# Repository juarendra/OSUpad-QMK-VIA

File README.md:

<div align="center">

# OSUpad Clone VIA

**Macropad 6 tombol hotswap + tactile dengan RGB — konfigurasi tombol, layer,
macro, dan efek RGB lewat VIA, tanpa driver tambahan.**

oleh [Juarendra Ramadhani](https://github.com/juarendra)

[📦 Unduh Firmware](https://github.com/juarendra/OSUpad-QMK-VIA/releases/latest) |
[📖 Panduan Pengguna](DOC/PANDUAN_OSUPAD.md) |
[💻 Buka VIA](https://usevia.app) |
[🛠️ Hardware](HARDWARE)

</div>

---

Firmware alternatif berbasis Arduino (VIA-Arduino) untuk *clone* Macropad OSUpad 2x3. Ditujukan untuk *board clone* STM32F103 (dengan flash 32KB/64KB/256KB) yang jalur USB-nya tidak stabil ketika menggunakan firmware QMK/ChibiOS bawaan.

- **Protokol Stabil:** Menggunakan *USB stack* `STM32duino/libmaple` yang teruji stabil untuk clone STM32.
- **Auto-Detect VIA:** Menggunakan USB VID `0x7877` dan PID `0x1000` (sama dengan QMK). Memungkinkan *auto-detect* di aplikasi VIA jika *cache* definisi sudah ada di browser Anda.
- **Lighting Responsif:** Dukungan penuh tab Lighting di VIA V3 dengan efek `qmk_rgblight` dan optimasi *timing* bit-bang khusus untuk LED WS2812 di clock 72MHz.
- **Penyimpanan Aman:** Dual-page Flash Storage melindungi konfigurasi Anda dari kerusakan data jika USB tiba-tiba dicabut.

## Panduan Cepat

1. Unduh rilis `.bin` terbaru dan ikuti panduan **[Flash ST-Link](FIRMWARE/OSUpadCloneVIA/FLASH_STLINK.md)**.
2. Cabut ST-Link, colok kabel USB, lalu buka [usevia.app](https://usevia.app).
3. Jika *auto-detect* gagal, buka tab **Settings**, aktifkan **Show Design Tab**, lalu *load* `via-definition.json` yang ada di rilis. Pastikan opsi *Use V2 definitions* dinonaktifkan.
4. Jangan lupa baca **[Buku Panduan OSUpad](DOC/PANDUAN_OSUPAD.md)** untuk referensi layer dan kustomisasi.

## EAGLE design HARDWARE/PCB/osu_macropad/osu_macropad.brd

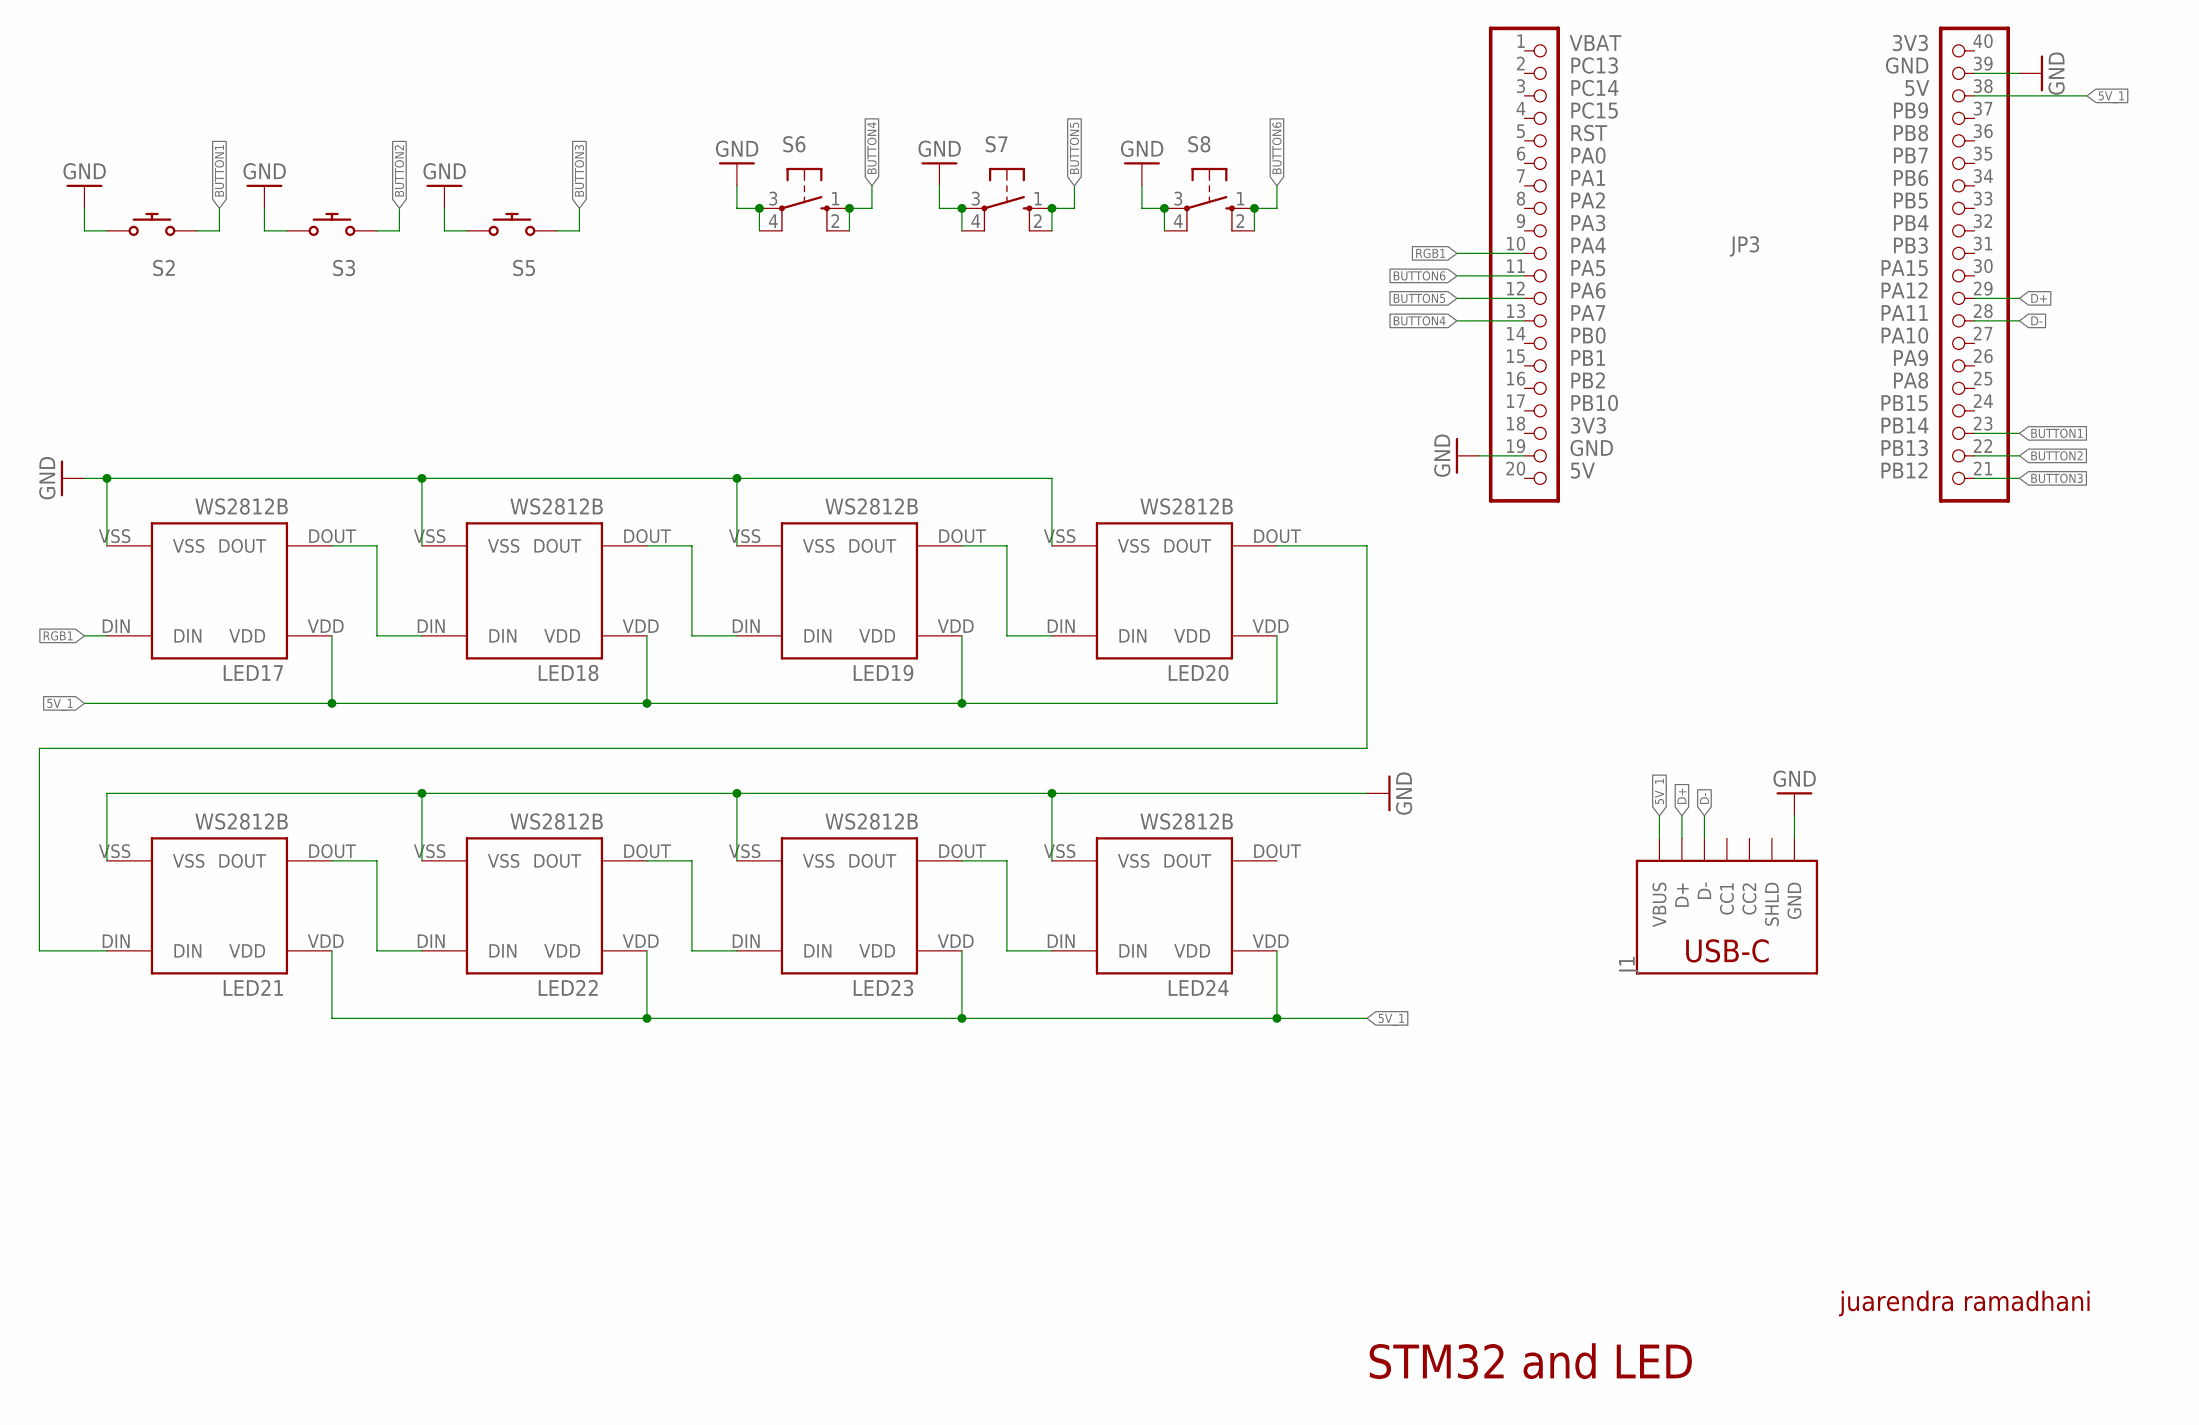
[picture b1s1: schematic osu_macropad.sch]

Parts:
J1: USB_C_2-LAYER_PADS; USB-C-16P-2LAYER-PADS
JP3: PINHD-1X20; 1X20
LED17, LED18, LED19, LED20, LED21, LED22, LED23, LED24: WS2812B
S2, S3, S5: CHERRY_MX_WITH_KEILWITH_KEIL; CHERRY_MX_WITH_KEIL
S6, S7, S8: 10-XX; B3F-10XX

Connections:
5V_1: J1.VBUS1 (VBUS), J1.VBUS2 (VBUS), JP3.38, LED17.VDD, LED18.VDD, LED19.VDD, LED20.VDD, LED21.VDD, LED22.VDD, LED23.VDD, LED24.VDD
BUTTON1: JP3.23, S2.2, S2.4 (2)
BUTTON2: JP3.22, S3.2, S3.4 (2)
BUTTON3: JP3.21, S5.2, S5.4 (2)
BUTTON4: JP3.13, S6.1 (S), S6.2 (S1)
BUTTON5: JP3.12, S7.1 (S), S7.2 (S1)
BUTTON6: JP3.11, S8.1 (S), S8.2 (S1)
D+: J1.A6 (D+), J1.B6 (D+), JP3.29
D-: J1.A7 (D-), J1.B7 (D-), JP3.28
GND: J1.GND, J1.GND2 (GND), JP3.19, JP3.39, LED17.VSS, LED18.VSS, LED19.VSS, LED20.VSS, LED21.VSS, LED22.VSS, LED23.VSS, LED24.VSS, S2.1, S2.3 (1), S3.1, S3.3 (1), S5.1, S5.3 (1), S6.3, S6.4 (P1), S7.3, S7.4 (P1), S8.3, S8.4 (P1)
unnamed: LED19.DOUT, LED20.DIN
unnamed: LED17.DOUT, LED18.DIN
unnamed: LED20.DOUT, LED21.DIN
unnamed: LED18.DOUT, LED19.DIN
unnamed: LED21.DOUT, LED22.DIN
unnamed: LED22.DOUT, LED23.DIN
unnamed: LED23.DOUT, LED24.DIN
RGB1: JP3.10, LED17.DIN

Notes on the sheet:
STM32 and LED
juarendra ramadhani

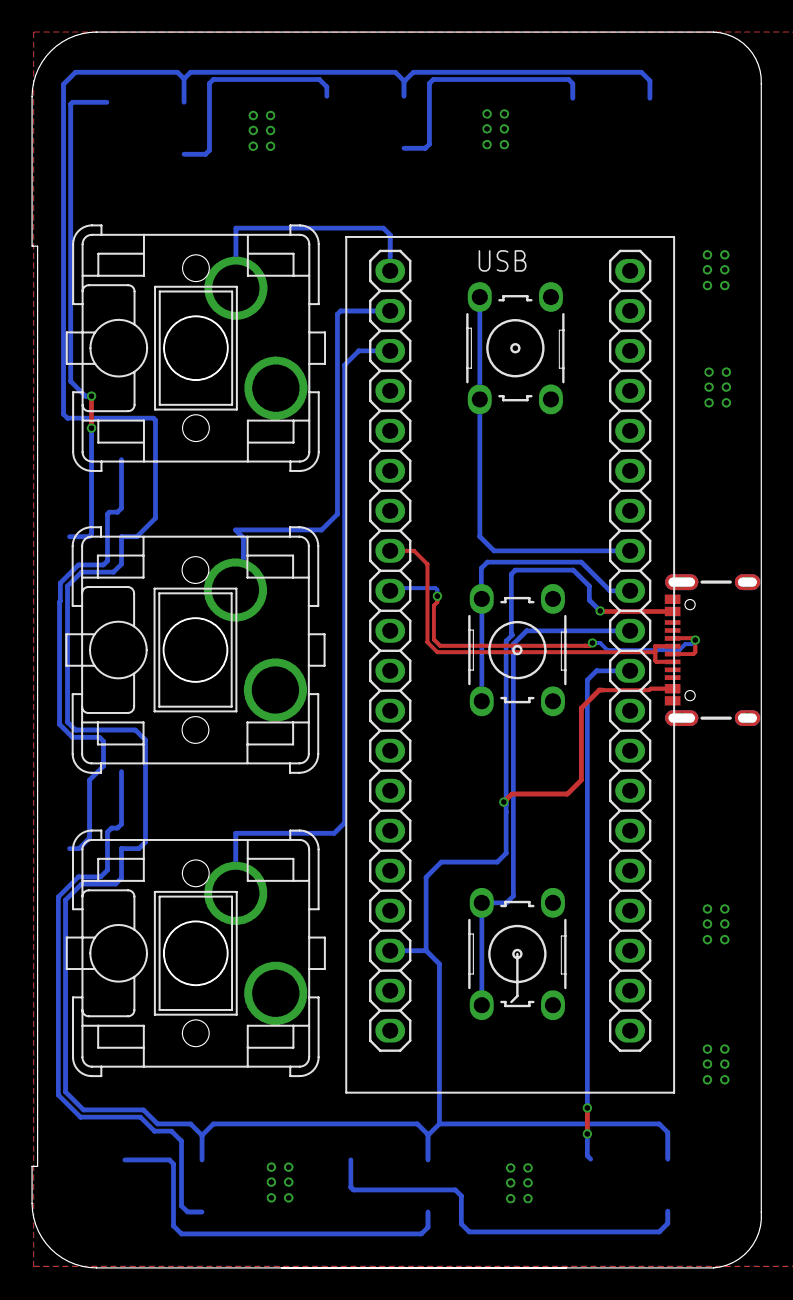
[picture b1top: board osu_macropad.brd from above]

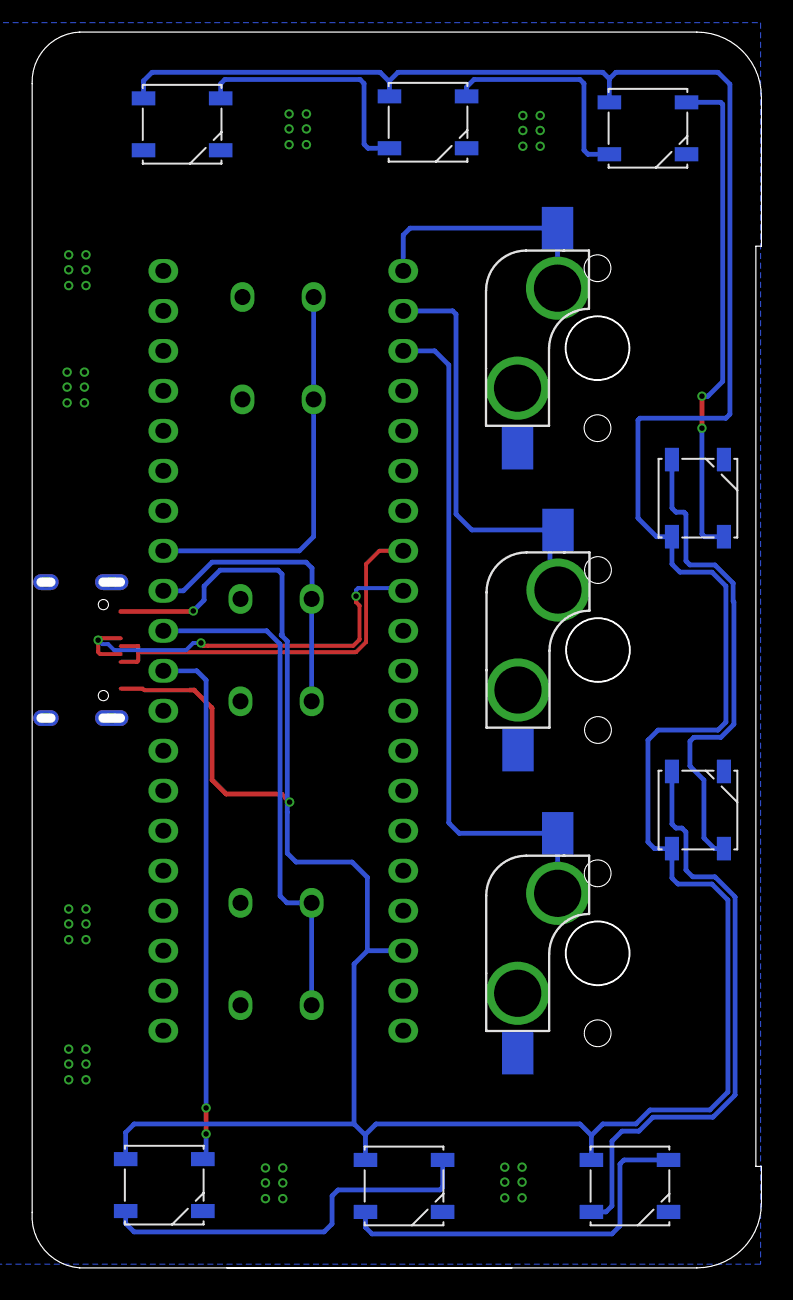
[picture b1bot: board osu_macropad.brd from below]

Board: 2 copper layers, 46.3 x 78.5 mm, 16 parts (8 on the bottom side), 18 nets.

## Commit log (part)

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2025-02-01 FEAT: add file some hardware
2025-02-01 FEAT: add 3d model
2025-02-01 FEAT: add PCB
2025-02-02 DOC: add readme documentation
2025-02-02 FEAT: add new image
2025-02-02 DOC: add image on readme
2025-02-03 FEAT: add firmware
2025-02-04 FEAT: add pid and vid
2025-02-04 FEAT: add flash firmware
2025-03-15 FEAT: update after testing on hardware
2025-05-08 FEAT: update manual documentation

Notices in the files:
parts and their libraries:
SparkFun-Connectors: Licensing: Creative Commons ShareAlike 4.0 International - https://creativecommons.org/licenses/by-sa/4.0
